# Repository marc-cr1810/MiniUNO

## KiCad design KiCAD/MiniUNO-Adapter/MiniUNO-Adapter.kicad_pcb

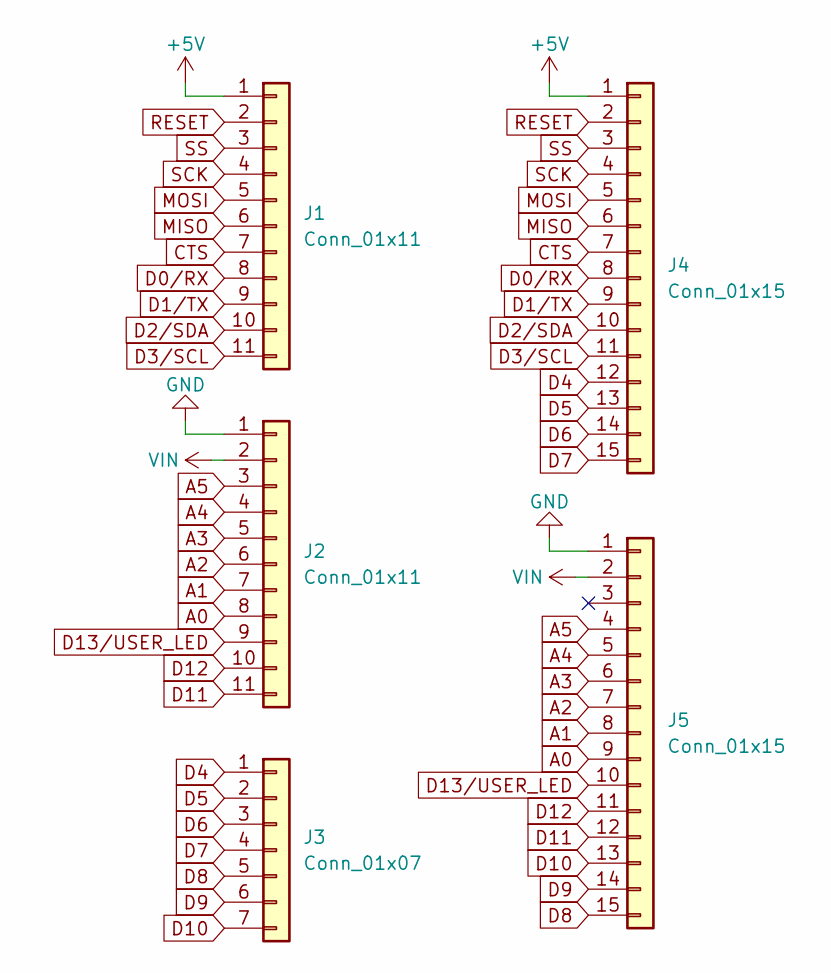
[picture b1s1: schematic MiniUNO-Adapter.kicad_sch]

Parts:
J1, J2: Conn_01x11; PinSocket_1x11_P2.00mm_Vertical
J3: Conn_01x07; PinSocket_1x07_P2.00mm_Vertical
J4, J5: Conn_01x15; PinHeader_1x15_P2.54mm_Vertical

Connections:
+5V: J1.1, J4.1
A0: J2.8, J5.9
A1: J2.7, J5.8
A2: J2.6, J5.7
A3: J2.5, J5.6
A4: J2.4, J5.5
A5: J2.3, J5.4
CTS: J1.7, J4.7
D0/RX: J1.8, J4.8
D1/TX: J1.9, J4.9
D2/SDA: J1.10, J4.10
D3/SCL: J1.11, J4.11
D4: J3.1, J4.12
D5: J3.2, J4.13
D6: J3.3, J4.14
D7: J3.4, J4.15
D8: J3.5, J5.15
D9: J3.6, J5.14
D10: J3.7, J5.13
D11: J2.11, J5.12
D12: J2.10, J5.11
D13/USER_LED: J2.9, J5.10
GND: J2.1, J5.1
MISO: J1.6, J4.6
MOSI: J1.5, J4.5
RESET: J1.2, J4.2
SCK: J1.4, J4.4
SS: J1.3, J4.3
VIN: J2.2, J5.2

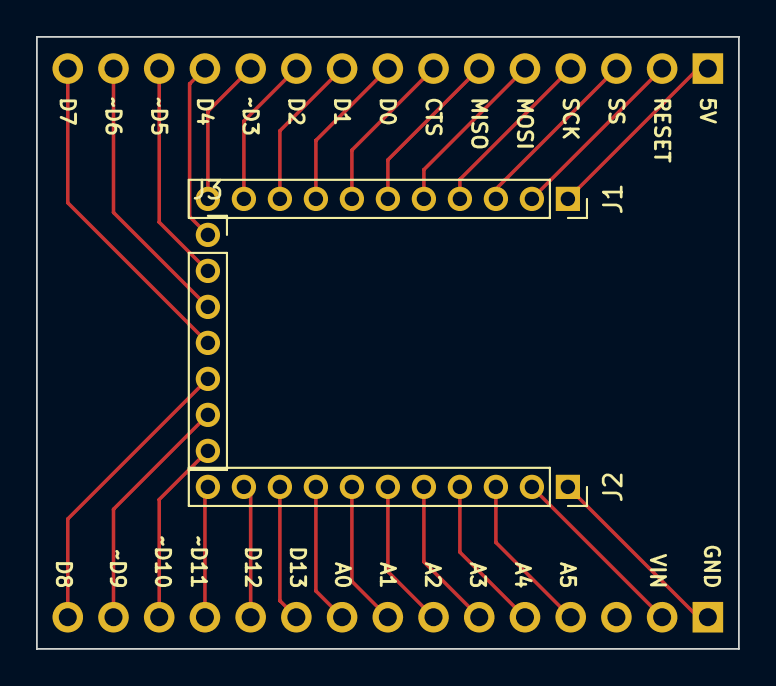
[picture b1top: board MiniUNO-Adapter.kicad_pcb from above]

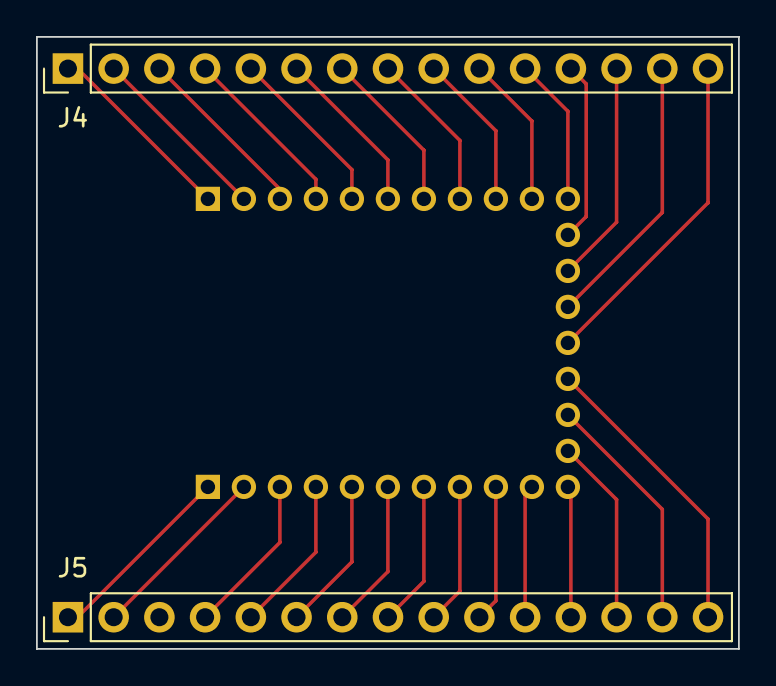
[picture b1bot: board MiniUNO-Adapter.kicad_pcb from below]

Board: 2 copper layers, 39.0 x 34.0 mm, 5 parts (2 on the bottom side), 29 nets.

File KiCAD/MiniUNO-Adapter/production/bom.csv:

Designator,Footprint,Quantity,Value,LCSC Part #
"J1, J2",PinSocket_1x11_P2.00mm_Vertical,2,Conn_01x11,
J3,PinSocket_1x07_P2.00mm_Vertical,1,Conn_01x07,
"J4, J5",PinHeader_1x15_P2.54mm_Vertical,2,Conn_01x15,

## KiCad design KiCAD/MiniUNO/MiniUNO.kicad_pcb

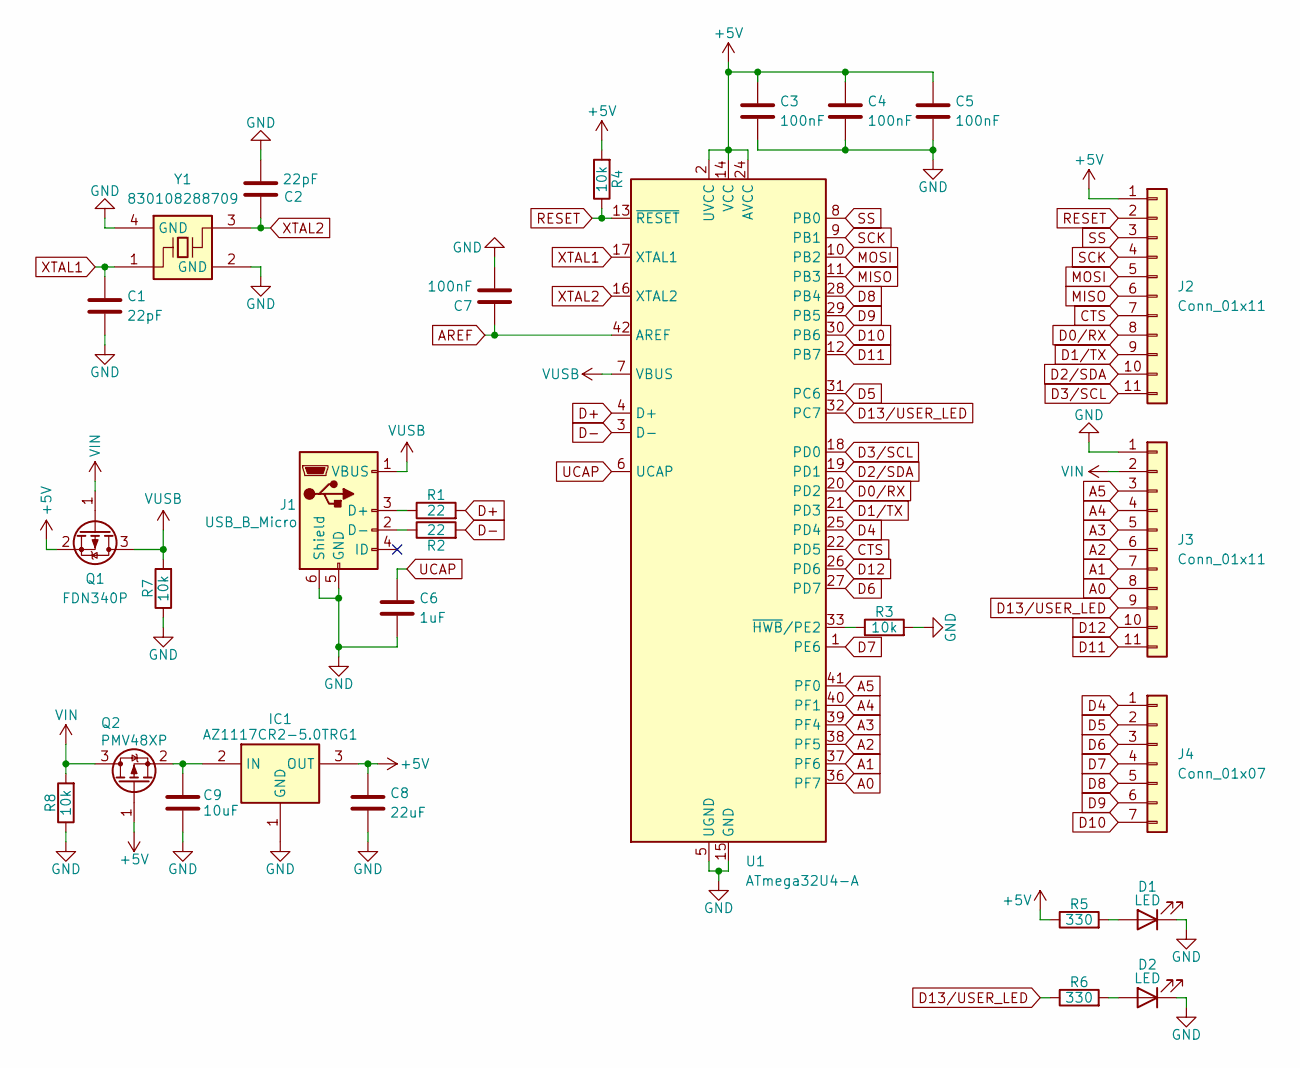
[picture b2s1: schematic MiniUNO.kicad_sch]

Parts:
C1, C2: 22pF; C_0603_1608Metric
C3, C4, C5, C7: 100nF; C_0603_1608Metric
C6: 1uF; C_0603_1608Metric
C8: 22uF; C_0603_1608Metric
C9: 10uF; C_0603_1608Metric
D1, D2: LED; LED_0603_1608Metric
IC1: AZ1117CR2-5.0TRG1; AP738133Y13; Mouser Part Number 621-AZ1117CR25.0TRG1
J1: USB_B_Micro; USB_Micro-B_GCT_USB3076-30-A
J2, J3: Conn_01x11; PinHeader_1x11_P2.00mm_Vertical
J4: Conn_01x07; PinHeader_1x07_P2.00mm_Vertical
Q1: FDN340P; SuperSOT-3
Q2: PMV48XP; SOT-23
R1, R2: 22; R_0603_1608Metric
R3, R4, R7, R8: 10k; R_0603_1608Metric
R5, R6: 330; R_0603_1608Metric
U1: ATmega32U4-A; TQFP-44_10x10mm_P0.8mm
Y1: 830108288709; 830108288709_Handsolderable; Mouser Part Number 710-830108288709

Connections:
+5V: C3.1, C4.1, C5.1, C8.1, IC1.3 (OUT), J2.1, Q1.2 (S), Q2.1 (G), R4.2, R5.1, U1.2 (UVCC), U1.14 (VCC), U1.24 (AVCC), U1.34 (VCC), U1.44 (AVCC)
A0: J3.8, U1.36 (PF7)
A1: J3.7, U1.37 (PF6)
A2: J3.6, U1.38 (PF5)
A3: J3.5, U1.39 (PF4)
A4: J3.4, U1.40 (PF1)
A5: J3.3, U1.41 (PF0)
AREF: C7.1, U1.42 (AREF)
CTS: J2.7, U1.22 (PD5)
D0/RX: J2.8, U1.20 (PD2)
D1/TX: J2.9, U1.21 (PD3)
D2/SDA: J2.10, U1.19 (PD1)
D3/SCL: J2.11, U1.18 (PD0)
D4: J4.1, U1.25 (PD4)
D5: J4.2, U1.31 (PC6)
D6: J4.3, U1.27 (PD7)
D7: J4.4, U1.1 (PE6)
D8: J4.5, U1.28 (PB4)
D9: J4.6, U1.29 (PB5)
D10: J4.7, U1.30 (PB6)
D11: J3.11, U1.12 (PB7)
D12: J3.10, U1.26 (PD6)
D13/USER_LED: J3.9, R6.1, U1.32 (PC7)
D+: R1.2, U1.4 (D+)
D-: R2.2, U1.3 (D-)
GND: C1.2, C2.2, C3.2, C4.2, C5.2, C6.2, C7.2, C8.2, C9.2, D1.1 (K), D2.1 (K), IC1.1 (GND), J1.5 (GND), J1.6 (Shield), J3.1, R3.2, R7.1, R8.1, U1.5 (UGND), U1.15 (GND), U1.23 (GND), U1.35 (GND), U1.43 (GND), Y1.2 (GND), Y1.4 (GND)
MISO: J2.6, U1.11 (PB3)
MOSI: J2.5, U1.10 (PB2)
unnamed: D1.2 (A), R5.2
unnamed: D2.2 (A), R6.2
unnamed: C9.1, IC1.2 (IN), Q2.2 (S)
unnamed: J1.3 (D+), R1.1
unnamed: J1.2 (D-), R2.1
unnamed: R3.1, U1.33 (~HWB/PE2)
RESET: J2.2, R4.1, U1.13 (~RESET)
SCK: J2.4, U1.9 (PB1)
SS: J2.3, U1.8 (PB0)
UCAP: C6.1, U1.6 (UCAP)
VIN: J3.2, Q1.1 (G), Q2.3 (D), R8.2
VUSB: J1.1 (VBUS), Q1.3 (D), R7.2, U1.7 (VBUS)
XTAL1: C1.1, U1.17 (XTAL1), Y1.1
XTAL2: C2.1, U1.16 (XTAL2), Y1.3

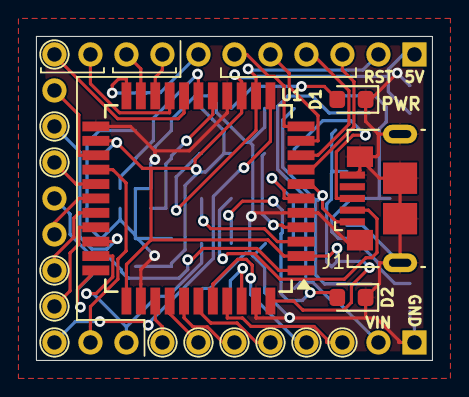
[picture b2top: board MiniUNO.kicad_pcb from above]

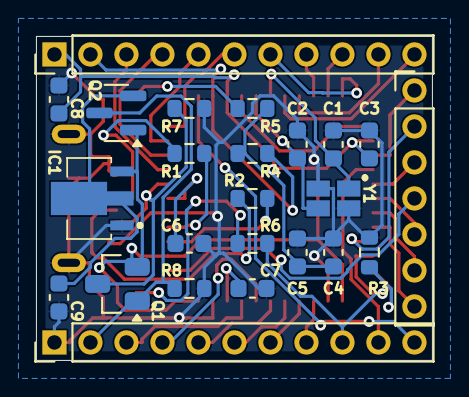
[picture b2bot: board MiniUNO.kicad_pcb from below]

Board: 2 copper layers, 22.0 x 18.0 mm, 28 parts (24 on the bottom side), 42 nets.

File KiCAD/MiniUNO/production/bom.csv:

Designator,Footprint,Quantity,Value,LCSC Part #
"C1, C2",0603,2,22pF,
"C3, C4, C5, C7",0603,4,100nF,
C6,0603,1,1uF,
C8,0603,1,22uF,
C9,0603,1,10uF,
"D1, D2",0603,2,LED,
IC1,AP738133Y13,1,AZ1117CR2-5.0TRG1,
J1,USB_Micro-B_GCT_USB3076-30-A,1,USB_B_Micro,
"J2, J3",PinHeader_1x11_P2.00mm_Vertical,2,Conn_01x11,
J4,PinHeader_1x07_P2.00mm_Vertical,1,Conn_01x07,
Q1,SuperSOT-3,1,FDN340P,
Q2,SOT-23,1,PMV48XP,
"R1, R2",0603,2,22,
"R3, R4, R7, R8",0603,4,10k,
"R5, R6",0603,2,330,
U1,TQFP-44_10x10mm_P0.8mm,1,ATmega32U4-A,
Y1,830108288709_Handsolderable,1,830108288709,

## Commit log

2025-05-04 Added a user controlled LED
2025-05-04 Minor changes
2025-05-06 Lots more work
2025-05-06 Addec pulldown resistors to the VUSB and VIN MOSFETS. Made the adapter PCB
2025-05-07 Finalized design v1
